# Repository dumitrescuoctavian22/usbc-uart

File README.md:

USB-C → UART Adapter

A compact USB-C to UART adapter designed around the CP2102 USB-to-UART bridge. The board provides a simple interface for connecting a computer to microcontrollers and other embedded systems through a standard UART interface.

The PCB was designed from schematic to layout in KiCad as a 2-layer board, with USB 2.0 connectivity, ESD protection, status LEDs, and an accessible UART header.

Features

- USB-C input
- CP2102 USB-to-UART bridge
- USB 2.0 interface
- USB ESD protection using ST USBLC6-2SC6
- 5-pin UART header
- Power and UART activity indicators
- 2-layer PCB
- Designed in KiCad

UART Header

The UART interface is exposed through a 5-pin header:

Pin| Function
1| RX

2| TX

3| 3V3

4| 5V

5| GND

USB-C Interface

The board uses a 16-pin USB-C receptacle for USB 2.0 communication.

The USB interface includes the USB data lines, power connections, and USB-C configuration connections. ESD protection is provided by the ST USBLC6-2SC6, protecting the USB data interface against electrostatic discharge.

USB-to-UART Conversion

The CP2102 is the main USB-to-UART bridge on the board.

It handles the conversion between USB communication from the host computer and the UART interface exposed on the header.

The board is intended to provide a convenient interface for development, debugging, and communication with embedded systems.

Status LEDs

Three LEDs are included on the board:

LED  | Color | Function

Power| Green | Power indication

RX   | Red   | UART receive activity

TX   | Yellow| UART transmit activity

These indicators provide visual feedback for power and UART communication.

PCB Design

The PCB was designed as a 2-layer board in KiCad.

The design process included:

- Schematic capture
- Component selection
- USB-C interface design
- USB ESD protection
- CP2102 USB-to-UART implementation
- Component placement
- PCB routing
- Power distribution
- UART header layout
- 3D PCB visualization

Particular attention was given to keeping the USB interface compact and placing the ESD protection around the USB connection.

Repository Structure

usbc-uart/

├── README.md

├── documentation/

├── hardware/

├── images/

└── manufacturing/

The repository contains the KiCad hardware design files, documentation, images, and manufacturing-related files.

Tools

- KiCad — schematic and PCB design
- KiCad 3D Viewer — PCB visualization

Project Status

PCB designed — not yet manufactured or tested.

This project currently represents the completed PCB design and serves as a practical demonstration of USB-C interfacing, USB-to-UART conversion, ESD protection, component placement, and 2-layer PCB routing.

What I Learned

This project was created to develop practical PCB design skills while working with a real USB interface and USB-to-UART bridge.

The main areas explored were:

- USB-C connector implementation
- USB 2.0 interface design
- USB ESD protection
- CP2102 integration
- UART interface design
- Power distribution
- PCB component placement
- 2-layer PCB routing
- KiCad schematic-to-PCB workflow
- PCB documentation and organization

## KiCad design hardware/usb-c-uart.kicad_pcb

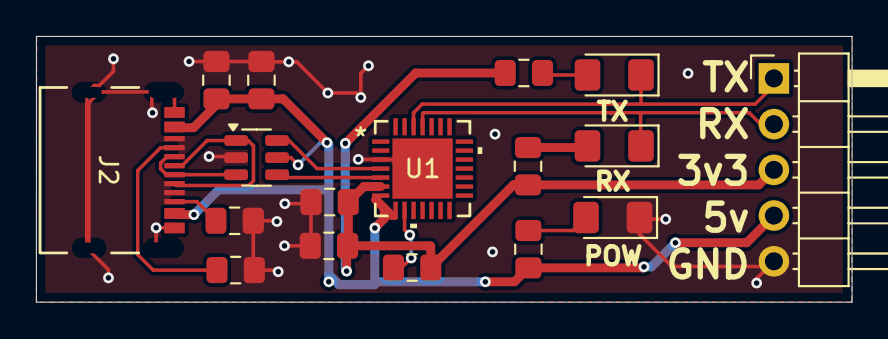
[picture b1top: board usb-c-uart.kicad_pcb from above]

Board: 2 copper layers, 45.3 x 14.8 mm, 17 parts (0 on the bottom side), 15 nets.

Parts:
C1: 1u; C_0805_2012Metric_Pad1.18x1.45mm_HandSolder
C2, C3: 100n; C_0805_2012Metric_Pad1.18x1.45mm_HandSolder
C4: 4u7; C_0805_2012Metric_Pad1.18x1.45mm_HandSolder
D1: GREEN P; LED_1206_3216Metric_Pad1.42x1.75mm_HandSolder
D2: YELLOW TX; LED_1206_3216Metric_Pad1.42x1.75mm_HandSolder
D3: RED RX; LED_1206_3216Metric_Pad1.42x1.75mm_HandSolder
J1: Conn_01x05_Pin; PinHeader_1x05_P2.54mm_Horizontal
J2: TYPE-C16PIN; CONN16_C16PIN_SHN
R1, R2: 5k1; C_0805_2012Metric_Pad1.18x1.45mm_HandSolder
R3, R5: 4k7; C_0805_2012Metric_Pad1.18x1.45mm_HandSolder
R4, R6: 2k2; C_0805_2012Metric_Pad1.18x1.45mm_HandSolder
U1: CP2102-GMR; QFN28_5X5_SIL
U2: USBLC6-2SC6; SOT-23-6

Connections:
GNDREF: C1.1, C2.1, C3.2, C4.2, D1.1 (K), J1.5, J2.A1 (GND), J2.A12 (GND), J2.B1 (GND), J2.B12 (GND), R1.2, R2.2, U1.3 (GND), U1.29 (EPAD), U2.2 (GND)
unnamed: D1.2 (A), R6.2
unnamed: D2.2 (A), R4.2
unnamed: D2.1 (K), J1.1, U1.26 (TXD)
unnamed: D3.2 (A), R5.2
unnamed: D3.1 (K), J1.2, U1.25 (RXD)
unnamed: J2.A5 (CC1), R2.1
unnamed: J2.B5 (CC2), R1.1
unnamed: J2.A7 (DN1), J2.B7 (DN2), U2.3 (I/O2)
unnamed: J2.A6 (DP1), J2.B6 (DP2), U2.1 (I/O1)
unnamed: R3.2, U1.9 (*RST)
unnamed: U1.4 (D+), U2.6 (I/O1)
unnamed: U1.5 (D-), U2.4 (I/O2)
VBUS: C1.2, C2.2, J1.4, J2.A4 (VBUS), J2.A9 (VBUS), J2.B4 (VBUS), J2.B9 (VBUS), R6.1, U1.7 (REGIN), U1.8 (VBUS), U2.5 (VBUS)
VDD: C3.1, C4.1, J1.3, R3.1, R4.1, R5.1, U1.6 (VDD)
